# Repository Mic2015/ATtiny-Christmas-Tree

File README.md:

# ATtiny-Christmas-Tree
Here is a project to create a mini Christmas tree (32x32mm) animated.
with these 8 LEDs smd he chained several figures you will also see the big version which measures about 7 cm
everything is programmed with Arduino and the core for Tiny
there is also a program with Delphi 7 that allows you to create and test your animations and to release the arduino code

Voici un projet qui permet de créer un mini sapin de Noël (32x32mm) animé.
avec à ces 8 LEDs smd il enchaine plusieurs figures vous verez aussi la version big qui mesure environ 7 cm
le tout est programmé avec Arduino et le core pour les Tiny
il y a aussi un programme céé avec delphi 7 qui permet de créer et tester   vos animation et de sortir le code arduino

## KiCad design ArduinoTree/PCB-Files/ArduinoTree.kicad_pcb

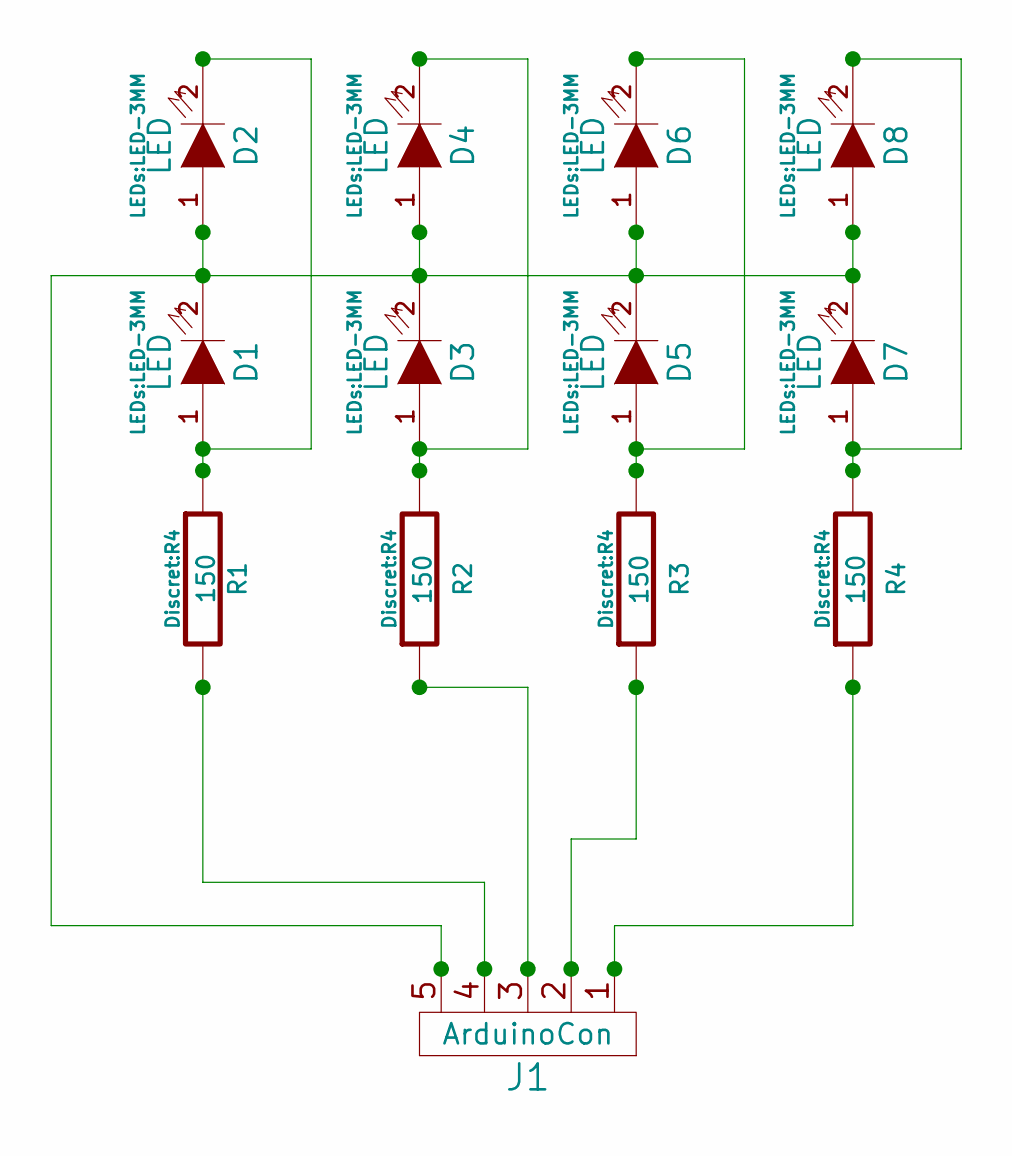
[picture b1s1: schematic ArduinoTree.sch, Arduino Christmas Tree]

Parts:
D1, D2, D3, D4, D5, D6, D7, D8: LED; LED-3MM
J1: ArduinoCon; pinhead-1X05
R1, R2, R3, R4: 150; R4

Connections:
unnamed: D1.1 (A), D2.2 (K), R1.1
unnamed: D1.2 (K), D2.1 (A), D3.2 (K), D4.1 (A), D5.2 (K), D6.1 (A), D7.2 (K), D8.1 (A), J1.5
unnamed: D3.1 (A), D4.2 (K), R2.2
unnamed: D5.1 (A), D6.2 (K), R3.2
unnamed: D7.1 (A), D8.2 (K), R4.2
unnamed: J1.1, R4.1
unnamed: J1.2, R3.1
unnamed: J1.3, R2.1
unnamed: J1.4, R1.2

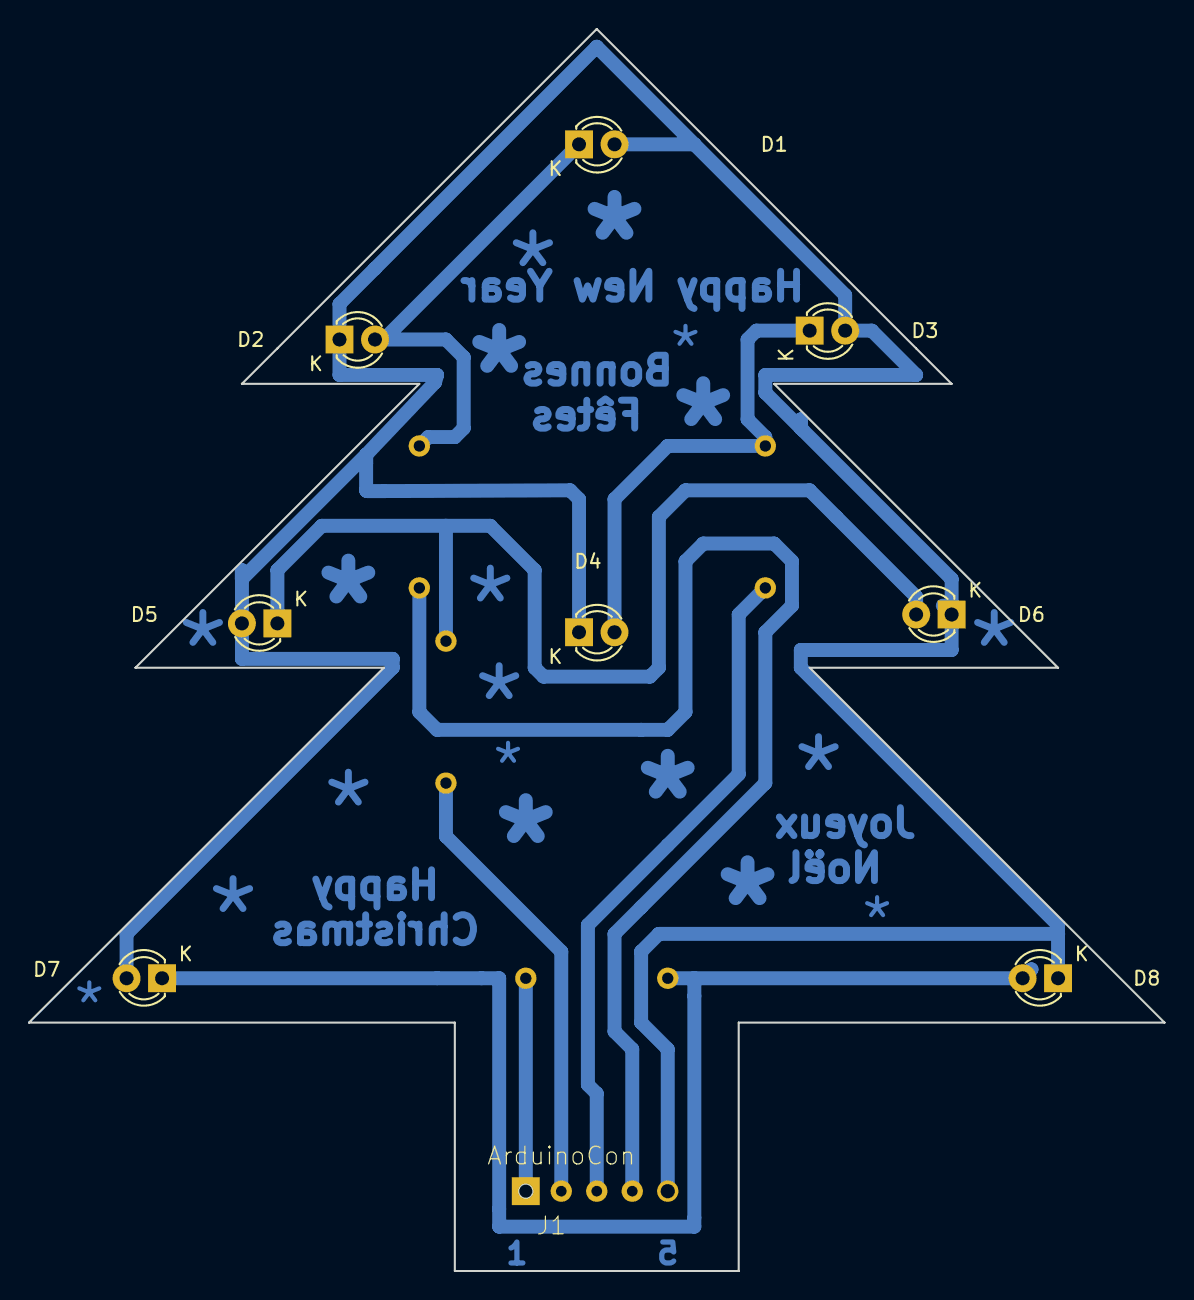
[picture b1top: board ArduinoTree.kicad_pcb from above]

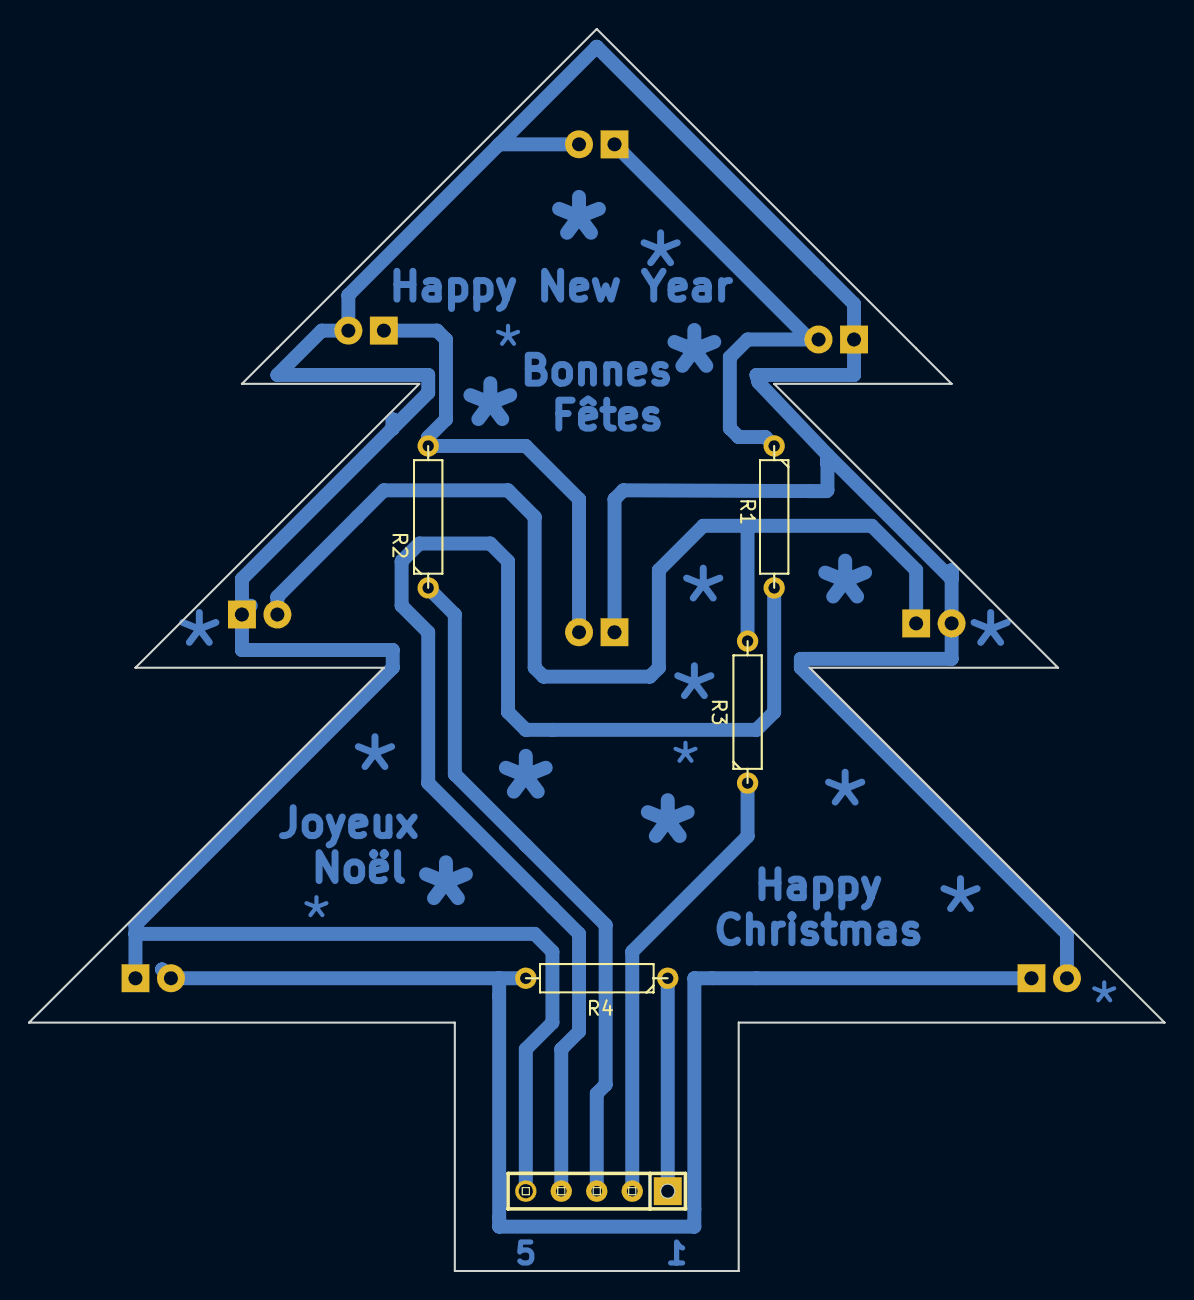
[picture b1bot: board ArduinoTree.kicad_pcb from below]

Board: 2 copper layers, 81.3 x 88.9 mm, 13 parts (5 on the bottom side), 9 nets.
